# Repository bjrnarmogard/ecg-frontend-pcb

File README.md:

# ecg-frontend-pcb
Compact 2-layer ECG analog front-end PCB designed in KiCad (INA126UA + TLC071ID + 1.65V ESP32 level shifter)
# ECG Analog Front-End PCB (KiCad)

Compact 2-layer PCB (`52 mm × 27 mm`) implementing a two-stage analog front-end for single-lead ECG acquisition, designed in KiCad and verified with **0 DRC errors and 0 warnings**.

## Circuit Architecture
1. **Stage 1 – Instrumentation Amplifier (`IC1: INA126UA`):**
   - Differential amplification with `R6 = 16 kΩ` (`Gain = 10 V/V`, `20 dB`) and high CMRR for 50 Hz common-mode noise rejection.
   - Local `100 nF` ceramic decoupling capacitors placed directly at `±15 V` supply pins.
2. **Stage 2 – Active Band-Pass Filter (`IC2: TLC071ID`):**
   - High-pass corner `~0.034 Hz` (`4.7 µF` + `1 MΩ`) to remove baseline wander, low-pass corner `~147 Hz` (`9 kΩ` || `120 nF`) to attenuate high-frequency noise, and `10×` (`20 dB`) gain (`1 + 9 kΩ / 1 kΩ`).
   - Local `100 nF` decoupling capacitors at `±5 V` supply pins.
3. **Level Shifter (`0–3.3 V` ADC Interface):**
   - AC-coupled (`4.7 µF`) into a `100 kΩ / 100 kΩ` divider biased at `1.65 V` for safe sampling by an `ESP32` ADC.
4. **PCB Layout & Testability:**
   - Solid bottom-layer `GND` plane (`B.Cu`) for noise shielding.
   - Four dedicated test points (`TP1`–`TP4`) for oscilloscope probing at each stage.
   - Production files included in `ecg-frontend-gerbers.zip`.

## Schematic & 3D View

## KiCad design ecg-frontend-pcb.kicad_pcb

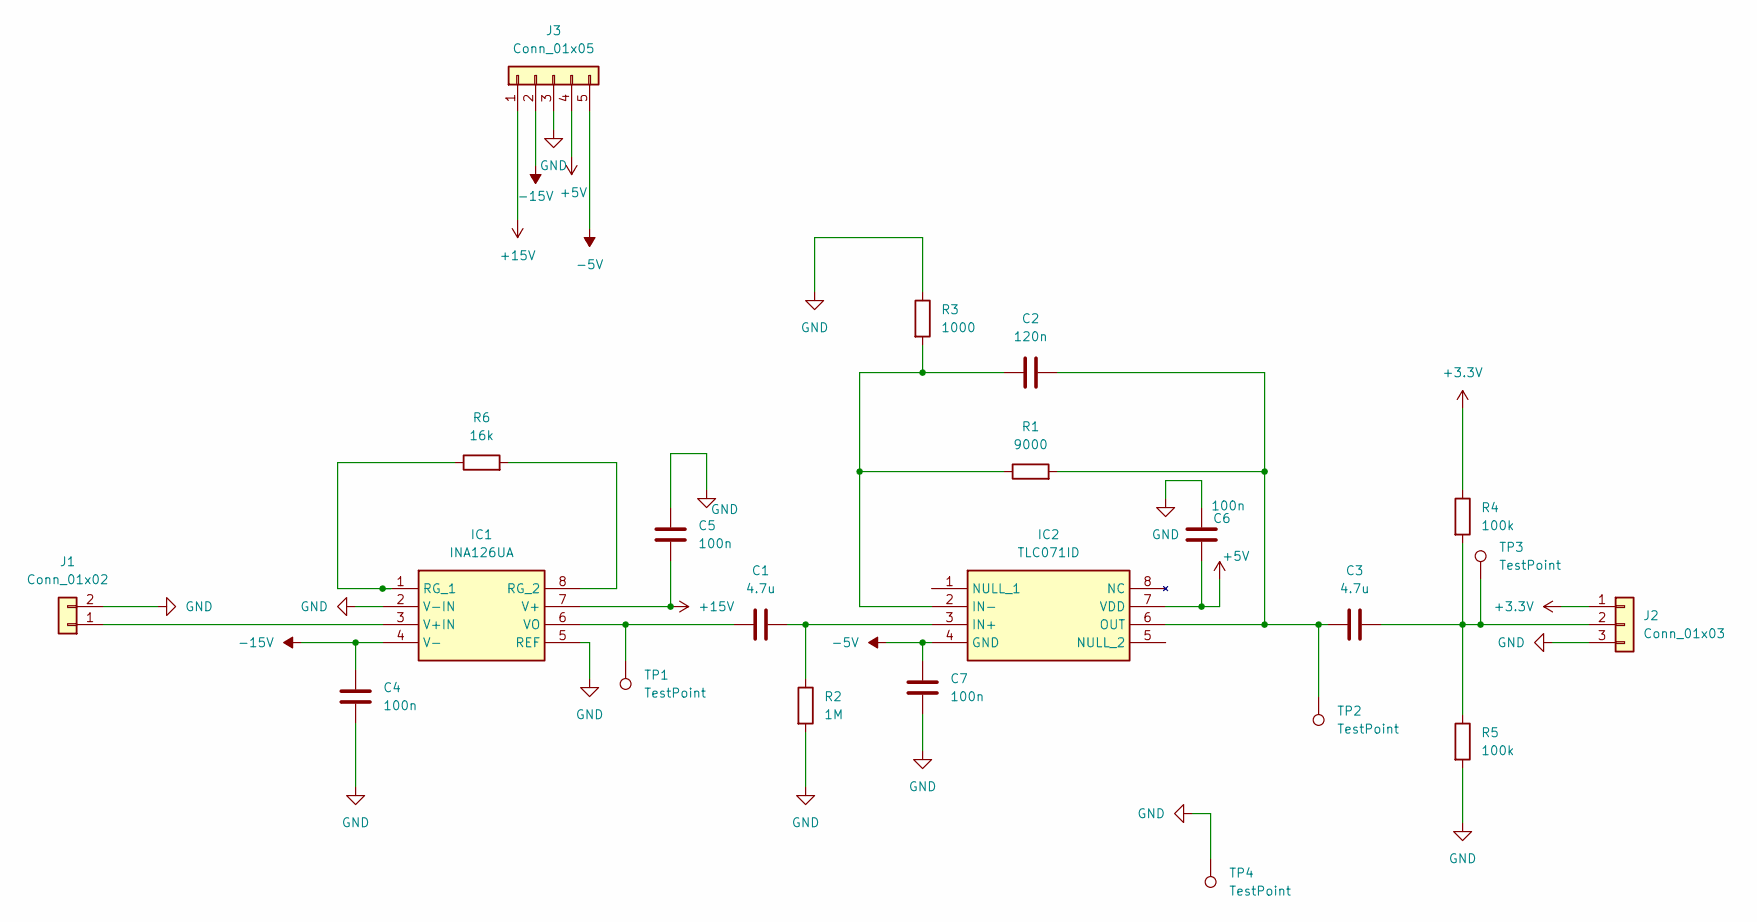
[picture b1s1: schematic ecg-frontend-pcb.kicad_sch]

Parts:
C1, C3: 4.7u; C_0805_2012Metric
C2: 120n; C_0805_2012Metric
C4, C5, C6, C7: 100n; C_0805_2012Metric
IC1: INA126UA; SOIC-8_3.9x4.9mm_P1.27mm; Mouser Part Number 595-INA126UA
IC2: TLC071ID; SOIC-8_3.9x4.9mm_P1.27mm; Mouser Part Number 595-TLC071ID
J1: Conn_01x02; PinHeader_1x02_P2.54mm_Vertical
J2: Conn_01x03; PinHeader_1x03_P2.54mm_Vertical
J3: Conn_01x05; PinHeader_1x05_P2.54mm_Vertical
R1: 9000; R_0805_2012Metric
R2: 1M; R_0805_2012Metric
R3: 1000; R_0805_2012Metric
R4, R5: 100k; R_0805_2012Metric
R6: 16k; R_0805_2012Metric
TP1, TP2, TP3, TP4: TestPoint; TestPoint_THTPad_D1.5mm_Drill0.7mm

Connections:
+3.3V: J2.1, R4.1
+5V: C6.2, IC2.7 (VDD), J3.4
+15V: C5.2, IC1.7 (V+), J3.1
-5V: C7.1, IC2.4 (GND), J3.5
-15V: C4.1, IC1.4 (V-), J3.2
GND: C4.2, C5.1, C6.1, C7.2, IC1.2 (V-IN), IC1.5 (REF), J1.2, J2.3, J3.3, R2.2, R3.1, R5.2, TP4.1 (1_1)
unnamed: IC1.1 (RG_1), R6.1
unnamed: IC1.8 (RG_2), R6.2
unnamed: IC1.3 (V+IN), J1.1
unnamed: C1.1, IC1.6 (VO), TP1.1 (1_1)
unnamed: C1.2, IC2.3 (IN+), R2.1
unnamed: C2.1, IC2.2 (IN-), R1.1, R3.2
unnamed: C2.2, C3.1, IC2.6 (OUT), R1.2, TP2.1 (1_1)
unnamed: C3.2, J2.2, R4.2, R5.1, TP3.1 (1_1)

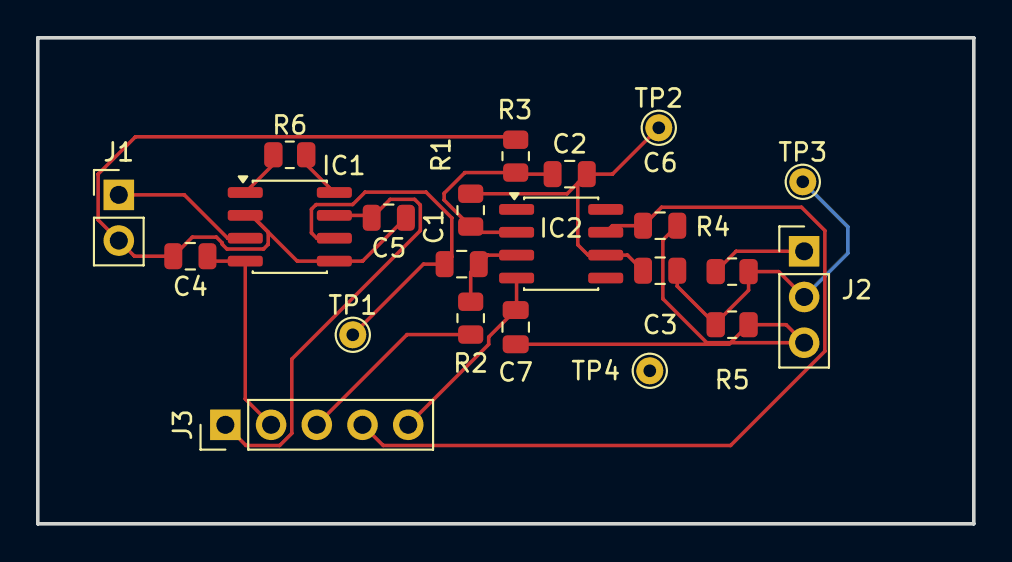
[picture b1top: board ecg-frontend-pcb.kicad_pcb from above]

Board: 2 copper layers, 52.0 x 27.0 mm, 22 parts (0 on the bottom side), 14 nets.
